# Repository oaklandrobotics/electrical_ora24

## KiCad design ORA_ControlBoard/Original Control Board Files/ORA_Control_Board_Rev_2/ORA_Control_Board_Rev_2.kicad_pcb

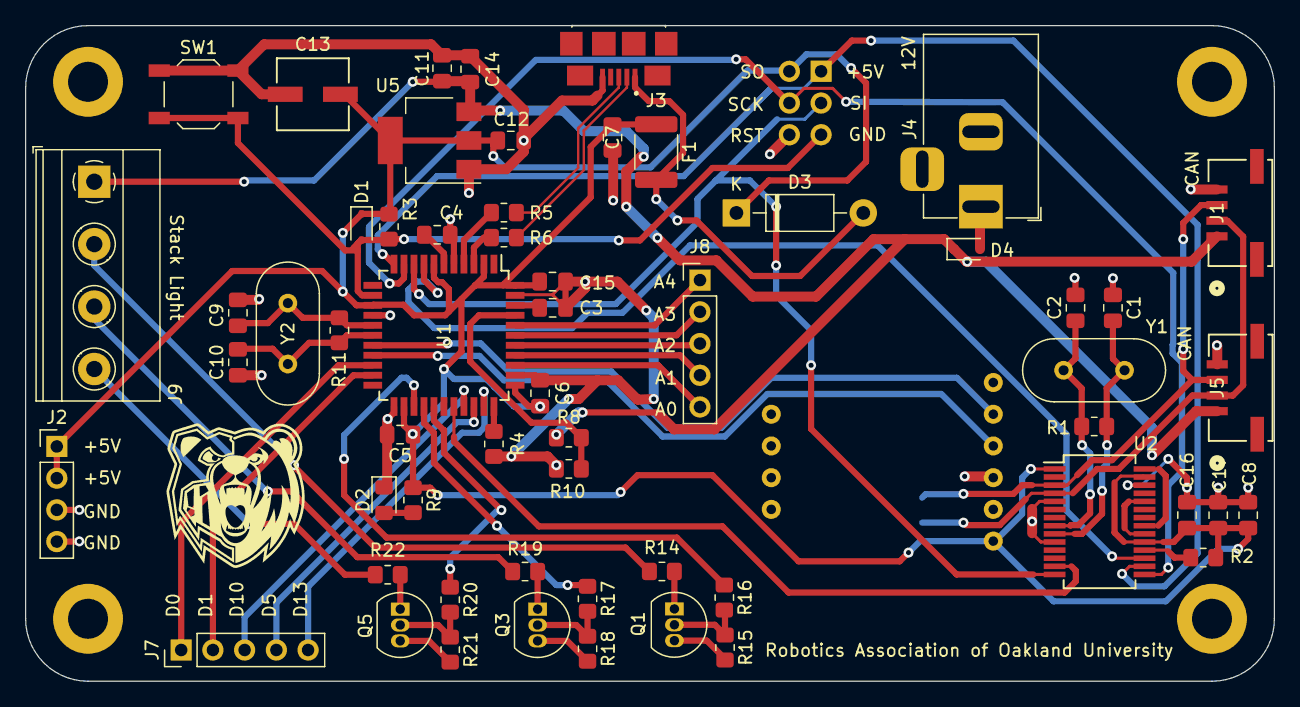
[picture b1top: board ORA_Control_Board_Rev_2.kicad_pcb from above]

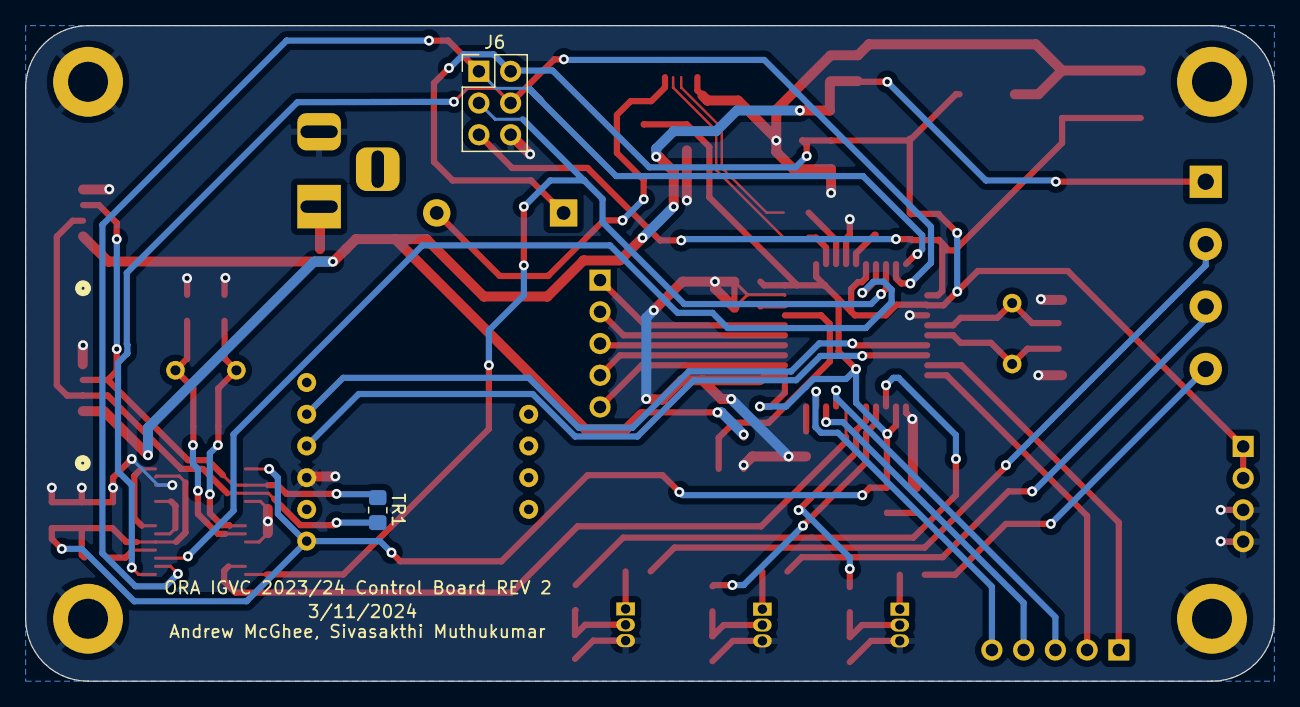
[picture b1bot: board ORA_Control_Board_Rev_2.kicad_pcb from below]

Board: 2 copper layers, 100.0 x 52.5 mm, 65 parts (2 on the bottom side), 53 nets.

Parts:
C1, C2, C9, C10: 22pF; C_0805_2012Metric_Pad1.18x1.45mm_HandSolder
C3, C5, C6, C8, C12, C14, C16, C17: 100nF; C_0805_2012Metric_Pad1.18x1.45mm_HandSolder
C4, C15: 1uF; C_0805_2012Metric_Pad1.18x1.45mm_HandSolder
C7: 10uF; C_0805_2012Metric_Pad1.18x1.45mm_HandSolder
C11: 10nF; C_0805_2012Metric_Pad1.18x1.45mm_HandSolder
C13: 22uF; CAP_WCAP-ASLI_05p0X05p5_WRE
D1: rst; D_SOD-323
D2: LED_Small; LED_0805_2012Metric_Pad1.15x1.40mm_HandSolder
D3: 1N5819; D_DO-41_SOD81_P10.16mm_Horizontal
D4: PWRIN; D_SOD-323
F1: MF-MSMF050-2; Fuse_1812_4532Metric_Pad1.30x3.40mm_HandSolder
H1, H2, H3, H4: MountingHole_Pad; MountingHole_3.2mm_M3_DIN965_Pad
J1, J5: SM04B-GHS-TB; CONN_SM04B-GHS-TB_JST
J2: Conn_01x04_Pin; PinHeader_1x04_P2.54mm_Vertical
J3: USB_B_Micro; AMPHENOL_10118192-0002LF
J4: 12V; BarrelJack_Horizontal
J6: Conn_02x03_Top_Bottom; PinHeader_2x03_P2.54mm_Vertical
J7, J8: Conn_01x05_Pin; PinHeader_1x05_P2.54mm_Vertical
J9: Stack Light; TerminalBlock_Phoenix_MKDS-1,5-4_1x04_P5.00mm_Horizontal
Q1, Q3, Q5: BS170; TO-92_Inline
R1, R11: 1M; R_0805_2012Metric_Pad1.20x1.40mm_HandSolder
R2, R3, R4, R14, R15, R18, R19, R21, R22: 10k; R_0805_2012Metric_Pad1.20x1.40mm_HandSolder
R5, R6: 22; R_0805_2012Metric_Pad1.20x1.40mm_HandSolder
R8: 2.2k; R_0805_2012Metric_Pad1.20x1.40mm_HandSolder
R9: 470; R_0805_2012Metric_Pad1.20x1.40mm_HandSolder
R10: 1.57k; R_0805_2012Metric_Pad1.20x1.40mm_HandSolder
R16, R17, R20: 1k; R_0805_2012Metric_Pad1.20x1.40mm_HandSolder
SW1: Reset; SW_SPST_TL3342
TR1: 120; R_0805_2012Metric_Pad1.20x1.40mm_HandSolder
U1: ATmega32U4-A; TQFP-44_10x10mm_P0.8mm
U2: MCP25625-x-SS; SSOP-28_5.3x10.2mm_P0.65mm
U5: NCP1117-5.0_SOT223; SOT-223-3_TabPin2
U6: IMU_MOUNT
Y1: 8Mhz; Crystal_HC49-4H_Vertical
Y2: 16MHz; Crystal_HC49-4H_Vertical

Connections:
(USB) D+: J3.3 (D+), R5.1
(USB) D-: J3.2 (D-), R6.2
+5V: C5.1, C6.1, C7.1, C8.1, C12.2, C13.1, C15.1, C16.1, C17.1, D1.1 (K), D3.1 (K), F1.1, J2.1, J2.2, J6.2, R2.1, R3.2, R9.1, U1.2 (UVCC), U1.7 (VBUS), U1.14 (VCC), U1.24 (AVCC), U1.34 (VCC), U1.44 (AVCC), U2.1 (VIO), U2.19 (VDD), U2.27 (VDDA), U5.2 (VO), U6.10 (Vin)
A0: J8.5, U1.36 (PF7)
A1: J8.4, U1.37 (PF6)
A2: J8.3, U1.38 (PF5)
A3: J8.2, U1.39 (PF4)
A4: J8.1, U1.40 (PF1)
CAN_CS: U1.8 (PB0), U2.17 (~CS)
CAN_H: J1.2, J5.2, TR1.2, U2.4 (CANH)
CAN_INT: U1.29 (PB5), U2.13 (~INT)
CAN_L: J1.3, J5.3, TR1.1, U2.3 (CANL)
CAN_SCK: J6.3, U1.9 (PB1), U2.14 (SCK)
CAN_SI: J6.4, U1.10 (PB2), U2.15 (SI)
CAN_SO: J6.1, U1.11 (PB3), U2.16 (SO)
D0: J7.1, U1.20 (PD2)
D1: J7.2, U1.21 (PD3)
D5: J7.4, U1.31 (PC6)
D10: J7.3, U1.30 (PB6)
D13: J7.5, U1.32 (PC7)
D+: R5.2, U1.4 (D+)
D-: R6.1, U1.3 (D-)
GND: C1.1, C2.2, C3.1, C4.1, C5.2, C6.2, C7.2, C8.2, C9.1, C10.2, C11.1, C12.1, C13.2, C14.1, C15.2, C16.2, C17.2, D2.1 (K), H1.1, H2.1, H3.1, H4.1, J1.4, J2.3, J2.4, J3.5 (GND), J4.2, J5.4, J6.6, Q1.3 (S), Q3.3 (S), Q5.3 (S), R4.2, R10.1, R15.2, R18.2, R21.2, SW1.1, U1.5 (UGND), U1.15 (GND), U1.23 (GND), U1.35 (GND), U1.43 (GND), U2.5 (STBY), U2.10 (GND), U2.26 (VSS), U5.1 (GND), U6.8 (GND)
IMU_SCL: U1.18 (PD0), U6.6 (SCL)
IMU_SDA: U1.19 (PD1), U6.7 (SDA)
LEDPWR_B: R20.1, U1.27 (PD7)
LEDPWR_G: R17.1, U1.26 (PD6)
LEDPWR_R: R16.1, U1.25 (PD4)
LED_B: J9.4, R22.1
LED_G: J9.3, R19.1
LED_R: J9.2, R14.1
unnamed: D2.2 (A), R9.2
unnamed: D3.2 (A), F1.2, J3.1 (VBUS)
unnamed: D4.2 (A), J4.1
unnamed: Q1.1 (D), R14.2
unnamed: Q1.2 (G), R15.1, R16.2
unnamed: Q3.1 (D), R19.2
unnamed: Q3.2 (G), R17.2, R18.1
unnamed: Q5.1 (D), R22.2
unnamed: Q5.2 (G), R20.2, R21.1
unnamed: C3.2, U1.42 (AREF)
unnamed: C4.2, U1.6 (UCAP)
unnamed: R4.1, U1.33 (~HWB/PE2)
unnamed: C1.2, R1.2, U2.9 (OSC1), Y1.2
unnamed: C2.1, R1.1, U2.8 (OSC2), Y1.1
unnamed: U2.21 (RxCAN), U2.28 (RXD)
unnamed: U2.20 (TxCAN), U2.24 (TXD)
unnamed: R2.2, U2.18 (~RESET)
Norm_Voltage: R8.2, R10.2, U1.41 (PF0)
PWRIN: C11.2, C14.2, D4.1 (K), J1.1, J5.1, J9.1, R8.1, U5.3 (VI)
RST: D1.2 (A), J6.5, R3.1, SW1.2, U1.13 (~RESET)
XTAL1: C10.1, R11.2, U1.17 (XTAL1), Y2.1
XTAL2: C9.2, R11.1, U1.16 (XTAL2), Y2.2

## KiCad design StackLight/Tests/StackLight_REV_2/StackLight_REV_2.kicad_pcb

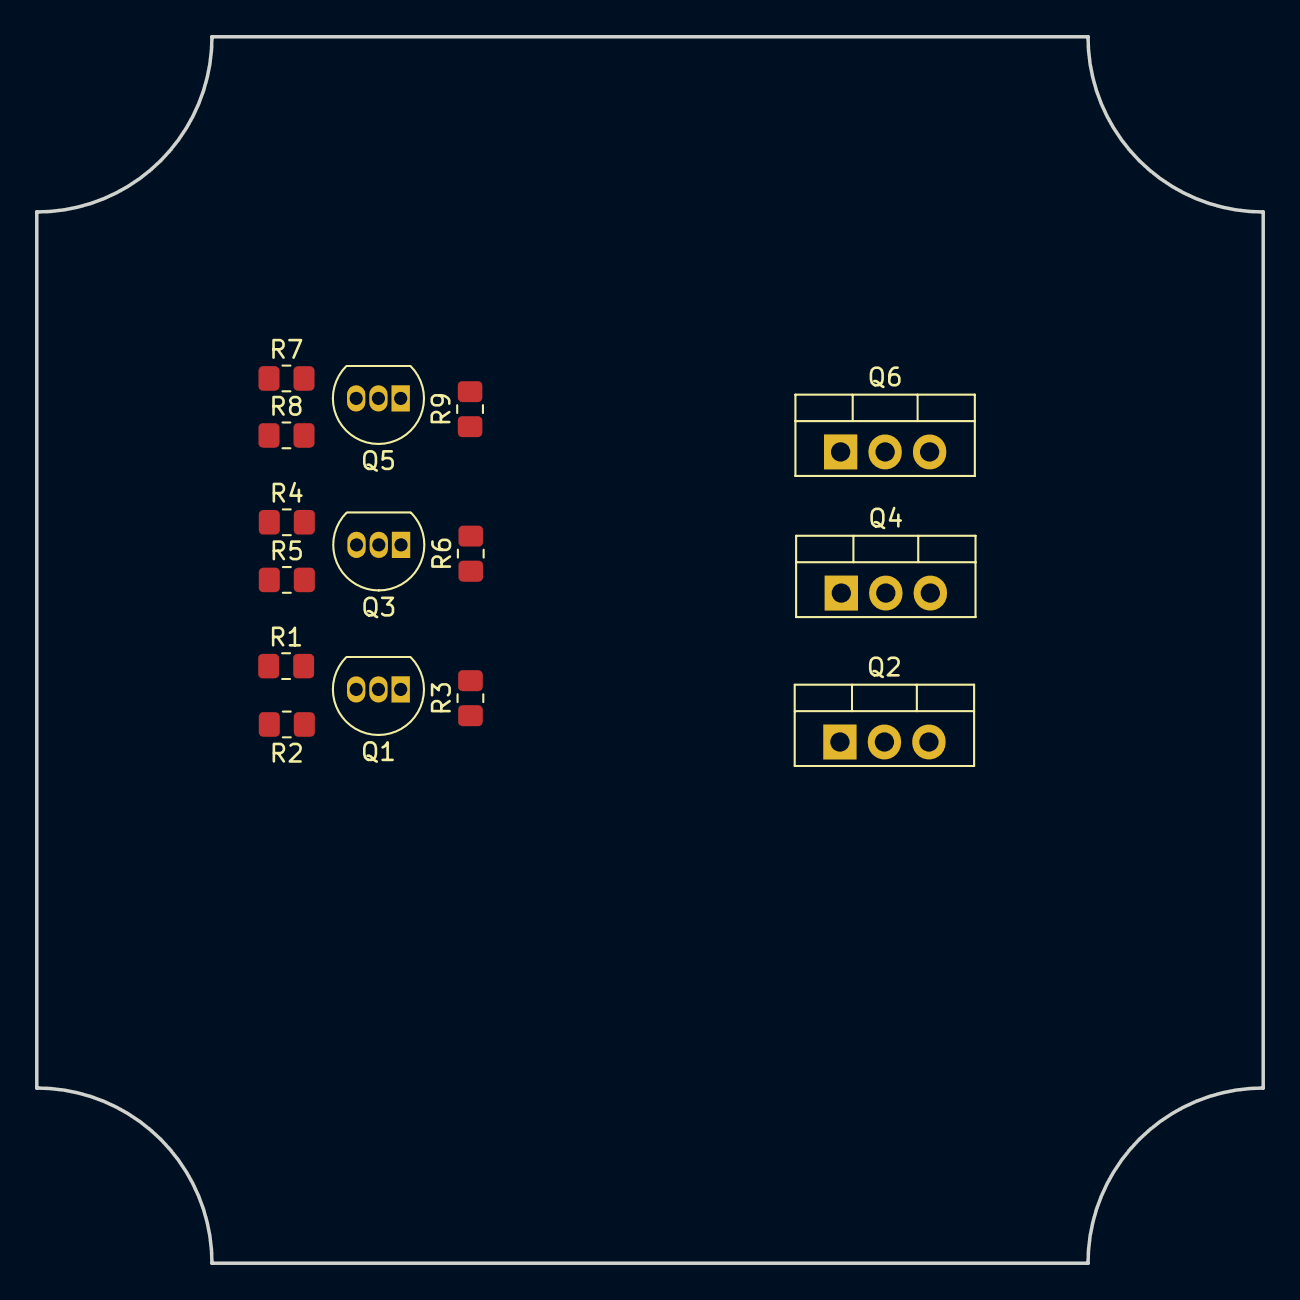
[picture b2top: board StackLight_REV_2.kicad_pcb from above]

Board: 2 copper layers, 70.0 x 70.0 mm, 15 parts (0 on the bottom side), 8 nets, no tracks yet.

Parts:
Q1, Q3, Q5: BS170; TO-92_Inline
Q2, Q4, Q6: IRF9540N; TO-220-3_Vertical
R1, R4, R7: 1k; R_0805_2012Metric_Pad1.20x1.40mm_HandSolder
R2, R3, R5, R6, R8, R9: 10k; R_0805_2012Metric_Pad1.20x1.40mm_HandSolder

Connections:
+12V: Q2.3 (S), Q4.3 (S), Q6.3 (S), R3.1, R6.1, R9.1
GND: Q1.3 (S), Q3.3 (S), Q5.3 (S), R2.1, R5.1, R8.1
unnamed: Q1.1 (D), Q2.1 (G), R3.2
unnamed: Q1.2 (G), R1.2, R2.2
unnamed: Q3.1 (D), Q4.1 (G), R6.2
unnamed: Q3.2 (G), R4.2, R5.2
unnamed: Q5.1 (D), Q6.1 (G), R9.2
unnamed: Q5.2 (G), R7.2, R8.2

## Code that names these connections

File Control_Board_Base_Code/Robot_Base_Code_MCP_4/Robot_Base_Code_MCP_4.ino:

#include <mcp_can.h>
#include <SPI.h>
#include <Wire.h>

// digital pins available on control board: 0, 1, 10, 5, 13
// analog pins available on control board: 0, 1, 2, 3, 4

// CAN / ODrive Declarations
#define ODRV0_NODE_ID 0 // Left Motor
#define ODRV1_NODE_ID 1 // Right Motor
#define CAN0_INT 2    // Set INT to pin 2 (This is the Interrupt pin)
#define CAN_BAUDRATE 500000
MCP_CAN CAN0(17);   // Set CS to pin 17 (This is the Chip select)

#define EStop 0         // Hardware EStop

// IMU Declarations
#define IMU_SCL 3 // On AtMega32U4 Connected to Pin 18 (PD0) // CHECK
#define IMU_SDA 2 // On AtMega32U4 Connected to Pin 19 (PD1)

// LED Declarations
#define LEDPWR_R 4 // On AtMega32U4 Connected to Pin 25 (PD4)
#define LEDPWR_G 12 // On AtMega32U4 Connected to Pin 26 (PD6)
#define LEDPWR_B 6 // On AtMega32U4 Connected to Pin 27 (PD7)

// Battery Voltage Detection Declaration
#define Battery_Voltage A0 // On AtMega32U4 Connected to Pin 27 (PF0)

double verticalMov = 0;
double horizontalMov = 0;
bool EStopButton = false;
bool EStopState = false;

void setup()
{
  Wire.begin(8);
  pinMode(EStop, INPUT);

  pinMode(CAN0_INT, INPUT);

  pinMode(IMU_SCL, INPUT); // Work on later
  pinMode(IMU_SDA, INPUT); // Work on later

  pinMode(LEDPWR_R, INPUT);
  pinMode(LEDPWR_G, INPUT);
  pinMode(LEDPWR_B, INPUT);

  pinMode(Battery_Voltage, INPUT);

  Serial.begin(115200);

  // Continuously tries to establish connection to MCP chip until it does
  while(1)
  {
    // Tries to initialize MCP CAN chip with clock of 8MHz and data transfer speed is 500KB/second
    if(CAN0.begin(MCP_ANY, CAN_500KBPS, MCP_8MHZ) == CAN_OK)
    {
      Serial.println("MCP2515 Initialized Successfully!");
      break;
    }
    else 
    {
      Serial.println("Error Initializing MCP2515...");
      delay(20);
    }
  }
}

void loop() 
{
  
  Wire.requestFrom(8, sizeof(int) + sizeof(int) + sizeof(bool)); // request data from slave device #8 (ESP32)
  
  // Checks to see if data is recieved over I2C. If so sets values from controller to predefined variables
  if(Wire.available() >= sizeof(int) + sizeof(int) + sizeof(bool)) // could combine with If statement below but this is easier to read for now
  {
    // Read vertical movement from left joystick
    int verticalMov = Wire.read();
    verticalMov |= Wire.read() << 8; // Combine with the next byte

    // Read horizontal movement from left joystick
    int horizontalMov = Wire.read();
    horizontalMov |= Wire.read() << 8; // Combine with the next byte

    // Read EStopButton from right bumper
    int EStopButton = Wire.read();
    
    // Print received values
    Serial.print("Received from ESP32 - Vertical Movement: ");
    Serial.println(verticalMov);

    Serial.print("Received from ESP32 - Horizontal Movement: ");
    Serial.println(horizontalMov);

    Serial.print("Received from ESP32 - EStop Button: ");
    Serial.println(EStopButton);

    delay(10);
  } 
  else
  {
    verticalMov = 0;
    horizontalMov = 0;
    EStopButton = false; // should it be true?
    Serial.println("Insufficient bytes received");
  }

  // Allows EStop to be toggled
  if(EStopButton && !EStopState)
  {
    // Send EStop command to ODrive
    ODriveEStop();
    EStopState = true;
  }
  else if(EStopButton && EStopState)
  {
    ODriveControlState();
    ODriveMovement(verticalMov, horizontalMov);
    EStopState = false;
  }
}

// Converts Joystick values into Revolutions/Second and sends data to ODrive over CAN
void ODriveMovement(double verticalVelocity, double horizontalVelocity) // redo math for turns/second
{
  // Scales inputs to directional vector
  verticalVelocity = constrain(verticalVelocity, -1.0, 1.0);
  horizontalVelocity = constrain(horizontalVelocity, -1.0, 1.0);

  // Standard for differential drive control
  double leftMotorVel = verticalVelocity - horizontalVelocity;
  double rightMotorVel = verticalVelocity + horizontalVelocity;

  // Converts the velocity requested into Revolutions / second
  const int maxVelocity = 5; // IGVC rules, should be meters/second units but not sure
  const double wheelCircumference = 2 * M_PI * 0.1524; // Circumference of the wheel in meters
  double leftMotorRPS= (leftMotorVel * maxVelocity) / wheelCircumference; // Turns/second
  double rightMotorRPS = (rightMotorVel * maxVelocity) / wheelCircumference; // Turns/second

  // Send velocity CAN commands to left and right motors
  CAN0.sendMsgBuf((ODRV0_NODE_ID << 5 | 0x0D), 0, 8, (byte*)&leftMotorRPS); // check 4
  CAN0.sendMsgBuf((ODRV1_NODE_ID << 5 | 0x0D), 0, 8, (byte*)&rightMotorRPS);
}

// Send CAN command to ODrive to initate EStop
void ODriveEStop()
{
  CAN0.sendMsgBuf((ODRV0_NODE_ID << 5 | 0x02), 0, 0, nullptr);
  CAN0.sendMsgBuf((ODRV1_NODE_ID << 5 | 0x02), 0, 0, nullptr);
  Serial.println("EStop Activated");
}

// Send CAN command to put axis into closed loop control state
void ODriveControlState() // Could combine with estop function but meh
{
  CAN0.sendMsgBuf((ODRV0_NODE_ID << 5 | 0x07), 0, 4, (byte*)"\x08");
  CAN0.sendMsgBuf((ODRV1_NODE_ID << 5 | 0x07), 0, 4, (byte*)"\x08");
  Serial.println("Put into closed loop control state");
}

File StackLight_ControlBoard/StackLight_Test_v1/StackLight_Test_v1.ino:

// States
bool EStopped = false;
bool AutonMode = false;

// Inputs
int LEDPWR_R = 0;
int LEDPWR_G = 1;
int LEDPWR_B = 10;
int EStop = 5;
int Auton = 13;

// Outputs
int LED_R = 4;
int LED_G = 12;
int LED_B = 6;

// Variables for blinking
unsigned long previousMillis = 0;
const long interval = 200; // Blink interval in milliseconds
bool LEDState = false;

void setup() {
  pinMode(LEDPWR_R, INPUT);
  pinMode(LEDPWR_G, INPUT);
  pinMode(LEDPWR_B, INPUT);
  pinMode(EStop, INPUT);
  pinMode(Auton, INPUT);

  pinMode(LED_R, OUTPUT);
  pinMode(LED_G, OUTPUT);
  pinMode(LED_B, OUTPUT);

  EStopped = true;
  AutonMode = false;
}

void loop() {
  EStopped = digitalRead(EStop);
  AutonMode = digitalRead(Auton);

  if (EStopped) { 
    EStopON();
  }
  else { 
    if (AutonMode) {
      BlinkBlueLED();
    }
    else {
      SolidGreenLED();
    }
  }
}

void EStopON() {
  digitalWrite(LED_B, LOW);
  digitalWrite(LED_G, LOW);
  digitalWrite(LED_R, HIGH); // Turn on the emergency stop LED
}

void BlinkBlueLED() {
  digitalWrite(LED_R, LOW);
  digitalWrite(LED_G, LOW);
  unsigned long currentMillis = millis();

  if (currentMillis - previousMillis >= interval) {
    previousMillis = currentMillis;

    // Toggle LED state
    LEDState = !LEDState;

    // Set LED accordingly
    digitalWrite(LED_B, LEDState ? HIGH : LOW);
  }
}

void SolidGreenLED() {
  // Turn on the green LED and turn off the blue LED
  digitalWrite(LED_B, LOW);
  digitalWrite(LED_G, HIGH);
  
}

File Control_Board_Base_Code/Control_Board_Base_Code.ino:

/* Pinouts:
--Internal--
Address PB1: SCK
Address PB2: MOSI
Address PB3: MISO
Address PB3/Digital 8: CS
Address PB5/Digital 9: INT

--External--
Analog0:
Analog1:
Analog2:
Analog3:
Analog4:

Digital 0: (RX)
Digital 1: (TX)
~Digital 5:
~Digital 10:
Digital 13:
*/

// Libraries Needed
#include "MCP2515.h"
#include "ODriveMCPCAN.hpp"
#include <SPI.h>

// ODrive & Can Definitions
#define CAN_BAUDRATE 500000
#define ODRV0_NODE_ID 0
MCP2515Class& can_intf = CAN; // Allows us to refer to can_intf as "CAN"

// MCP2515 Definitions
#define MCP2515_CS 8
#define MCP2515_INT 9
#define MCP2515_CLK_HZ 8000000

// Callback function to handle received CAN messages
static inline void receiveCallback(int packet_size) {
  if (packet_size > 8) {
    return;
  }
  CanMsg msg = {.id = (unsigned int)CAN.packetId(), .len = (uint8_t)packet_size};
  CAN.readBytes(msg.buffer, packet_size);
  onCanMessage(msg);
}

// Function to set up CAN communication
bool setupCan() {
  CAN.setPins(MCP2515_CS, MCP2515_INT);
  CAN.setClockFrequency(MCP2515_CLK_HZ);
  if (!CAN.begin(CAN_BAUDRATE)) {
    return false;
  }

  CAN.onReceive(receiveCallback);
  return true;
}

// Declaration of ODriveCAN instance and array of ODrive instances
ODriveCAN odrv0(wrap_can_intf(can_intf), ODRV0_NODE_ID);
ODriveCAN* odrives[] = {&odrv0};

// Struct to hold ODrive user data
struct ODriveUserData {
  Heartbeat_msg_t last_heartbeat;
  bool received_heartbeat = false;
  Get_Encoder_Estimates_msg_t last_feedback;
  bool received_feedback = false;
};

ODriveUserData odrv0_user_data;

// Callback function to handle received Heartbeat messages
void onHeartbeat(Heartbeat_msg_t& msg, void* user_data) {
  ODriveUserData* odrv_user_data = static_cast<ODriveUserData*>(user_data);
  odrv_user_data->last_heartbeat = msg;
  odrv_user_data->received_heartbeat = true;
}

// Function to handle incoming CAN messages
void onCanMessage(const CanMsg& msg) {
  for (auto odrive: odrives) {
    onReceive(msg, *odrive);
  }
}

// Setup function
void setup() {
  Serial.begin(115200);
  delay(200);

  if (!setupCan()) {
    Serial.println("CAN failed to initialize: reset required");
    while (true); 
  }

  Serial.println("Waiting for ODrive...");
  while (!odrv0_user_data.received_heartbeat) {
    pumpEvents(can_intf);
    delay(100);
  }

  Serial.println("found ODrive");
}

// Loop function
void loop() {
  pumpEvents(can_intf);
}

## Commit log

2023-09-26 Created file for ODrive Testing
2023-09-27 Created Arduino for testing
2023-11-04 Implement basic ODrive connection code
    Taken from the example code provided by ODrive, currently moves the motor in a jerky sine wave.
2023-11-11 Change to setting velocity targets from computer
    Inputting negative numbers should set the target velocity to 0, only positive numbers inputs affect the target velocity
2023-11-26 Moved Stacklight
2023-12-01 Testing was done
2024-02-17 I think this works
2024-02-17 W.I.P
2024-03-01 Updated
    Todo:
    Check pin PB0 connection on board
2024-03-01 Added Board Files
    Added the raw board files outside of a zip so they could be opened in KiCAD and updated accordingly without needing to send a zip file back and forth
2024-03-07 Rev_1.1
2024-03-08 Add files via upload
    Work in progress
2024-03-09 Uploaded Rev 2
2024-03-10 Spring Cleaning
2024-03-10 Updated LED circuit
2024-03-10 Fixed Spring Cleaning
2024-03-11 Finished Rev 2
2024-03-11 Updated USB B micro footprint
2024-03-11 Grounded mounting holes, labelled terminating resistors
2024-03-11 Moved ISP pins to back of board
2024-03-11 le testing
2024-03-11 "Final" Rev 2 changes
2024-03-12 I generated a gerber :/
2024-03-30 Control board program and ESP program completed.
    Still need to test sending CAN signals to ODrive
2024-04-01 Revision
    Things changed:
    VBUS flag added in between fuse and schottky diode (check this)
    Got rid of C7 and GND to VBUS pin on ATmega
    Changed silkscreen for ISP pins
2024-04-03 Rev 2.1
    Things changed:
    VBUS flag added in between fuse and schottky diode
    Got rid of C7 and GND to VBUS pin on ATmega
    Make CAN_H and CAN_L traces differential pairs
2024-04-17 I fixed a name lol
    Oops
2024-04-19 Added ESP32 Program and Reorganized program that work
2024-04-21 Added original control board files for rev 2
    They are put in different folder to make sure nothing is messed up hopefully.
2024-05-20 Software communication added
2024-06-01 Updated Arduino and ESP Program
    Logic for differential drive is still not working properly
2024-06-02 IGVC Updated Programs
2024-09-20 Update ps4 mac address
